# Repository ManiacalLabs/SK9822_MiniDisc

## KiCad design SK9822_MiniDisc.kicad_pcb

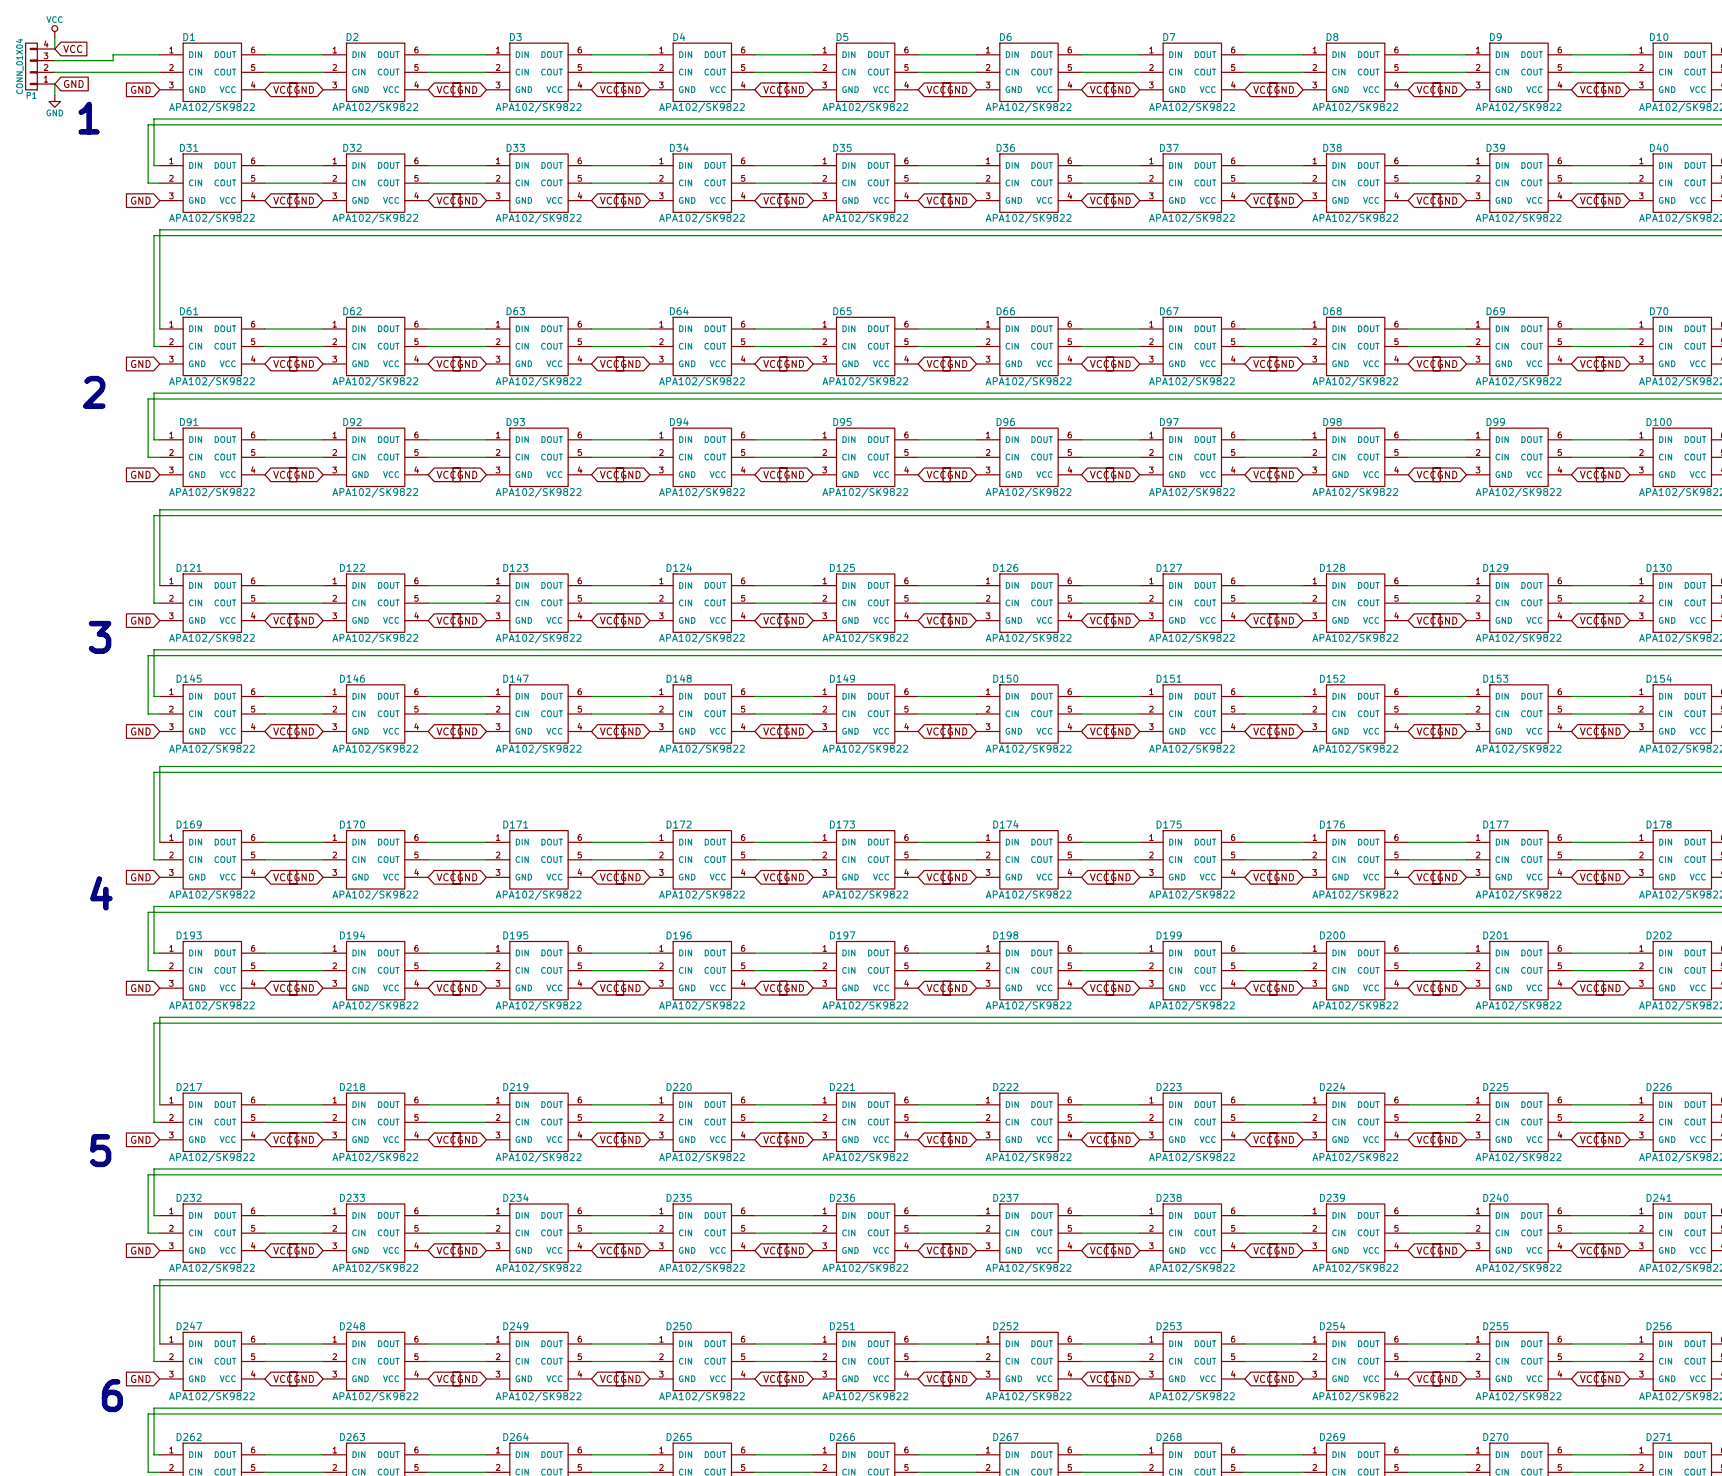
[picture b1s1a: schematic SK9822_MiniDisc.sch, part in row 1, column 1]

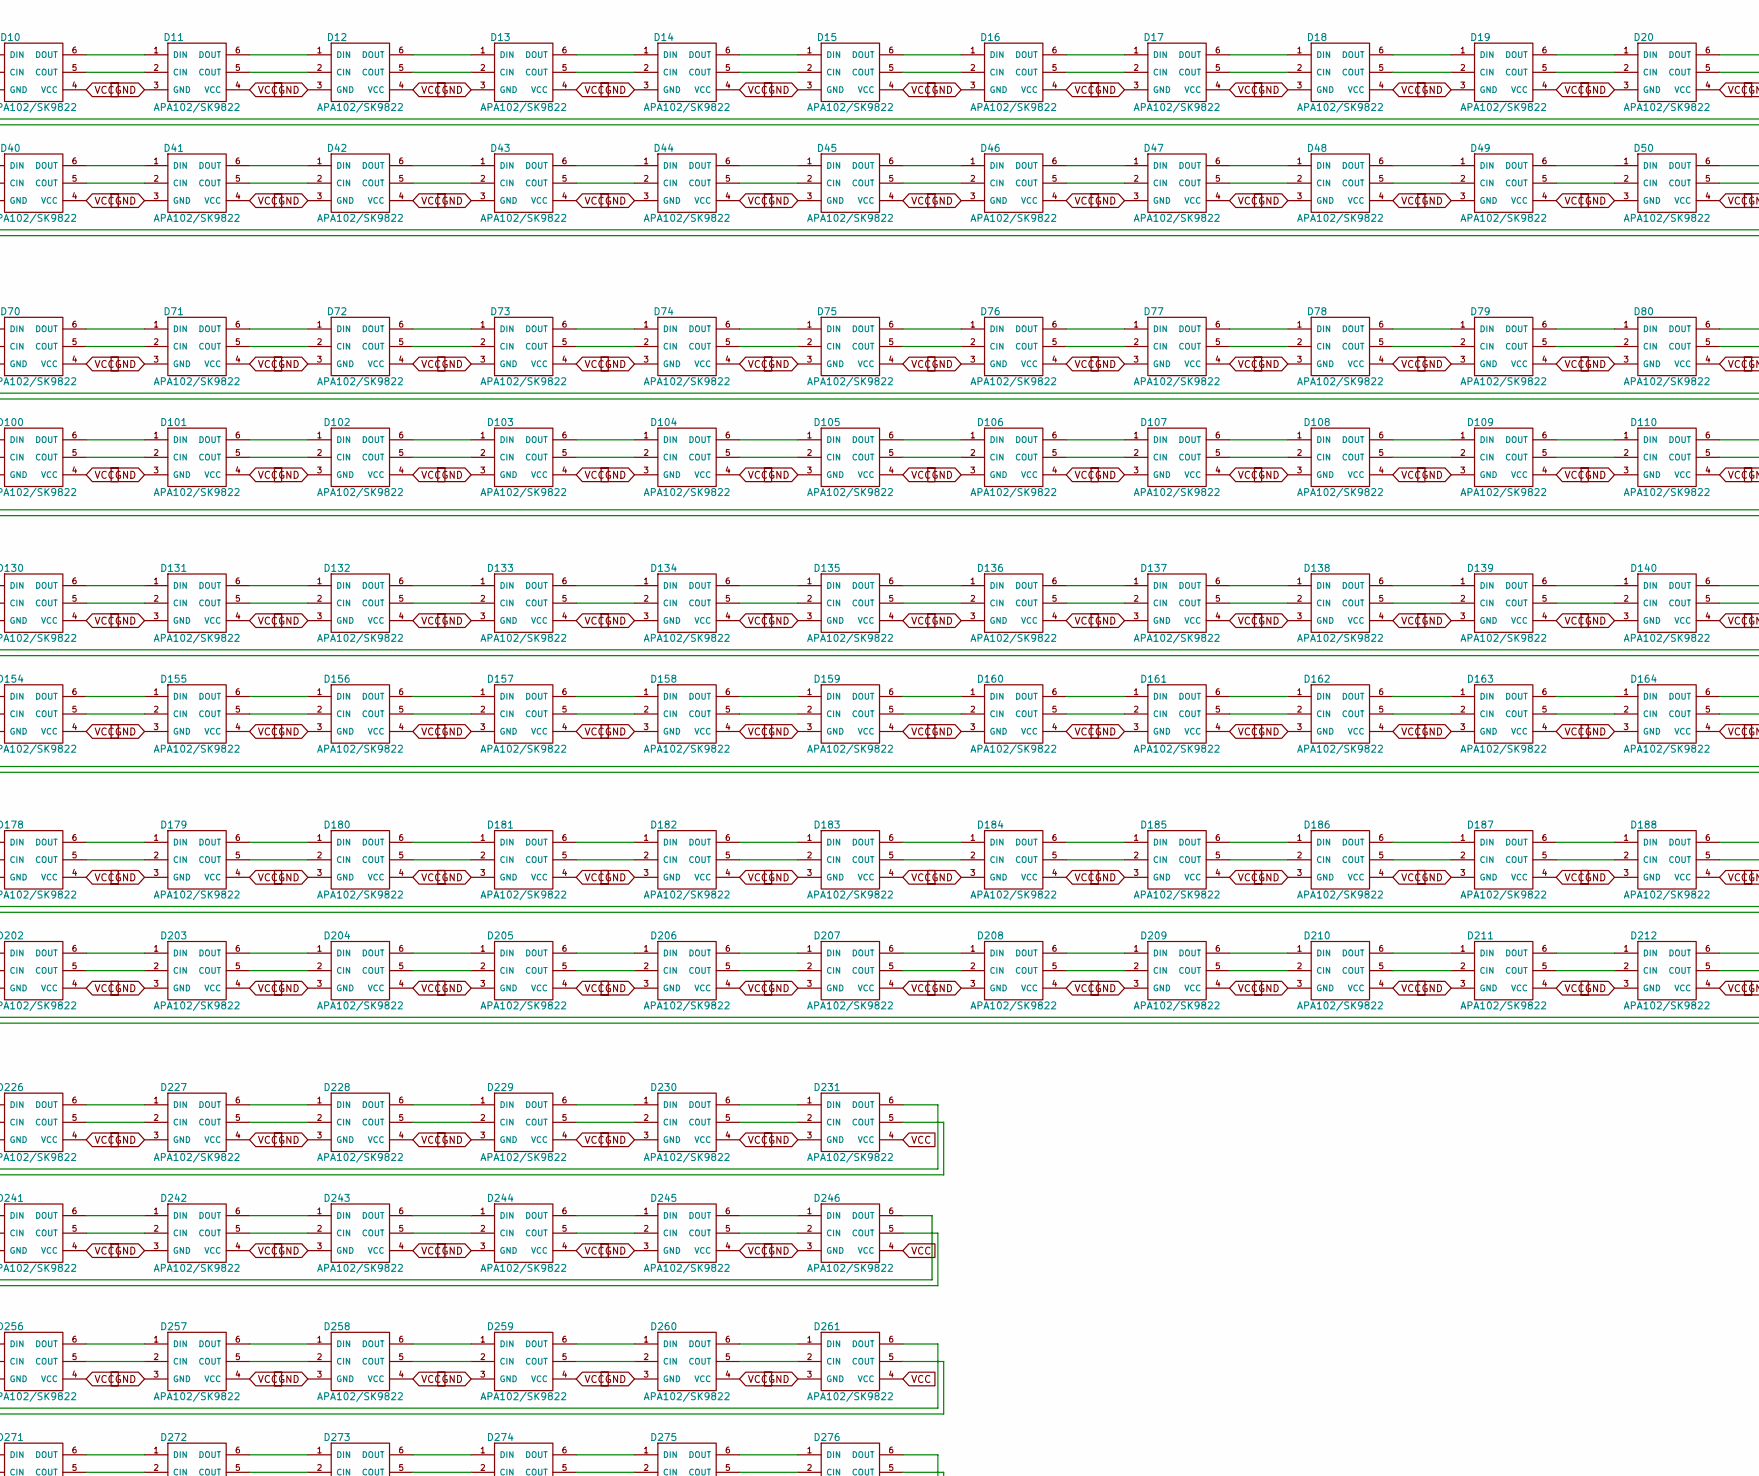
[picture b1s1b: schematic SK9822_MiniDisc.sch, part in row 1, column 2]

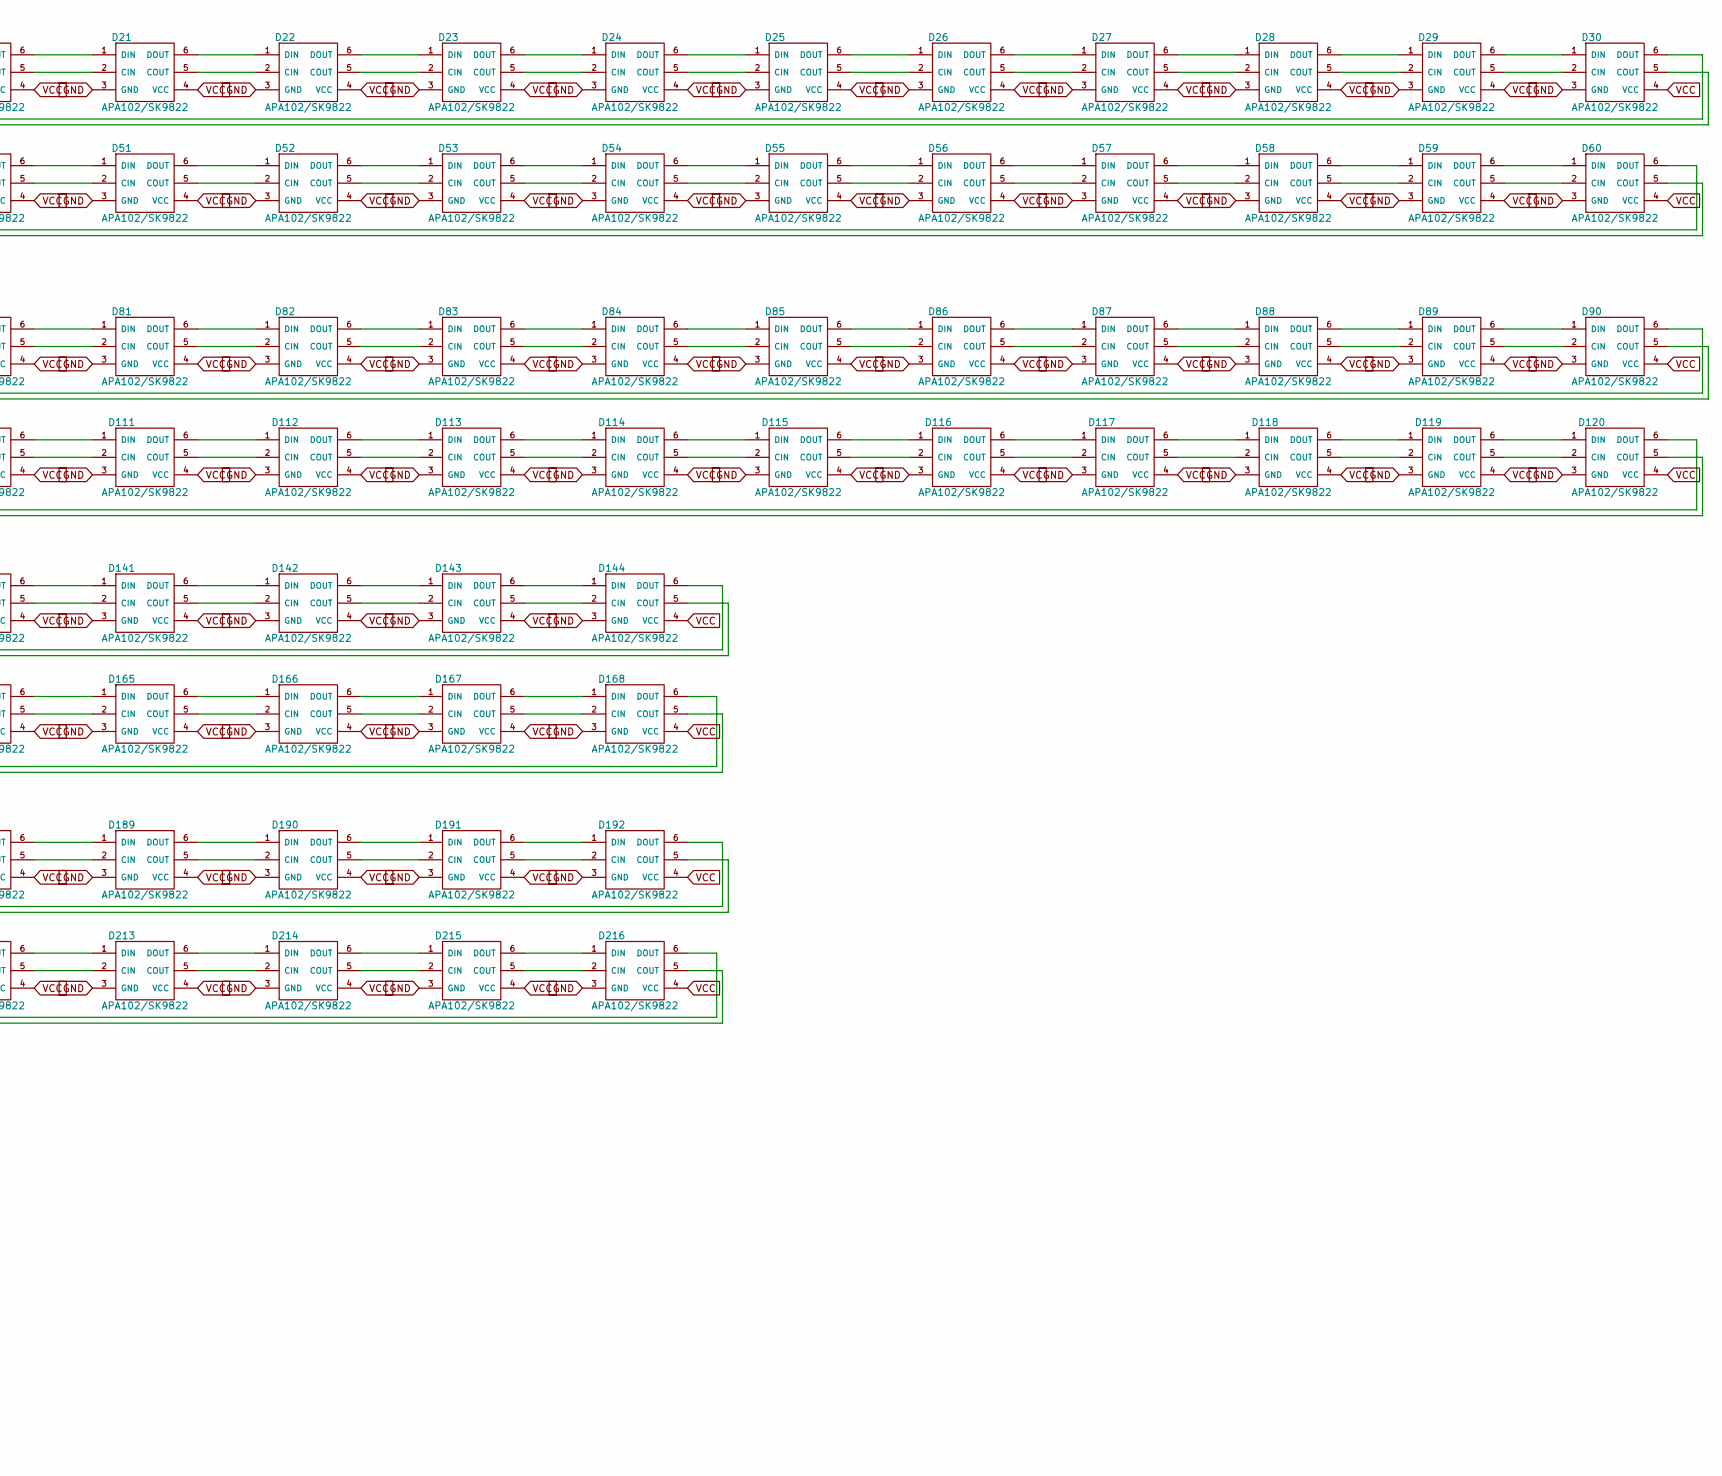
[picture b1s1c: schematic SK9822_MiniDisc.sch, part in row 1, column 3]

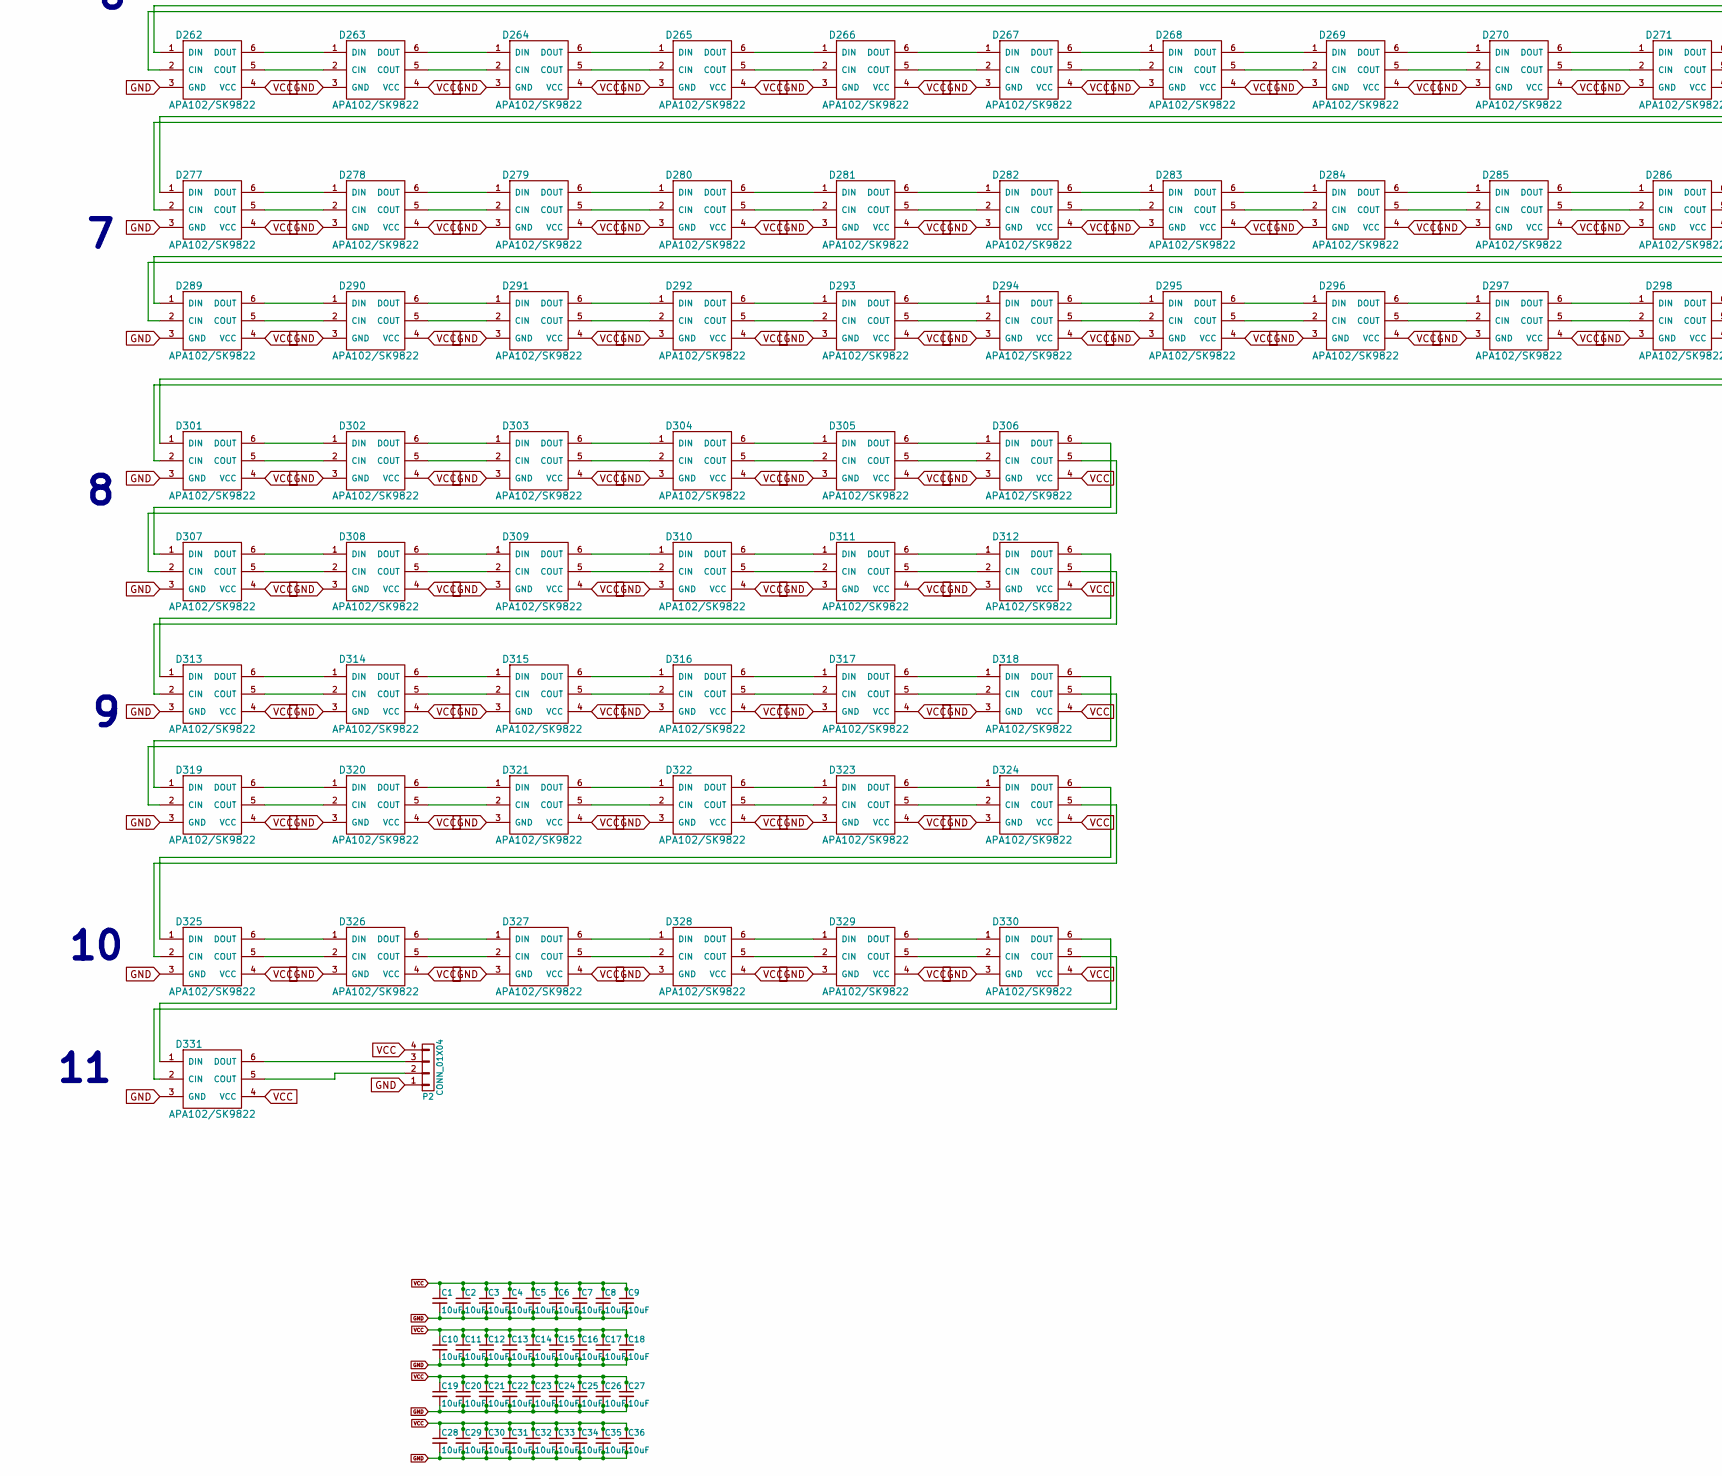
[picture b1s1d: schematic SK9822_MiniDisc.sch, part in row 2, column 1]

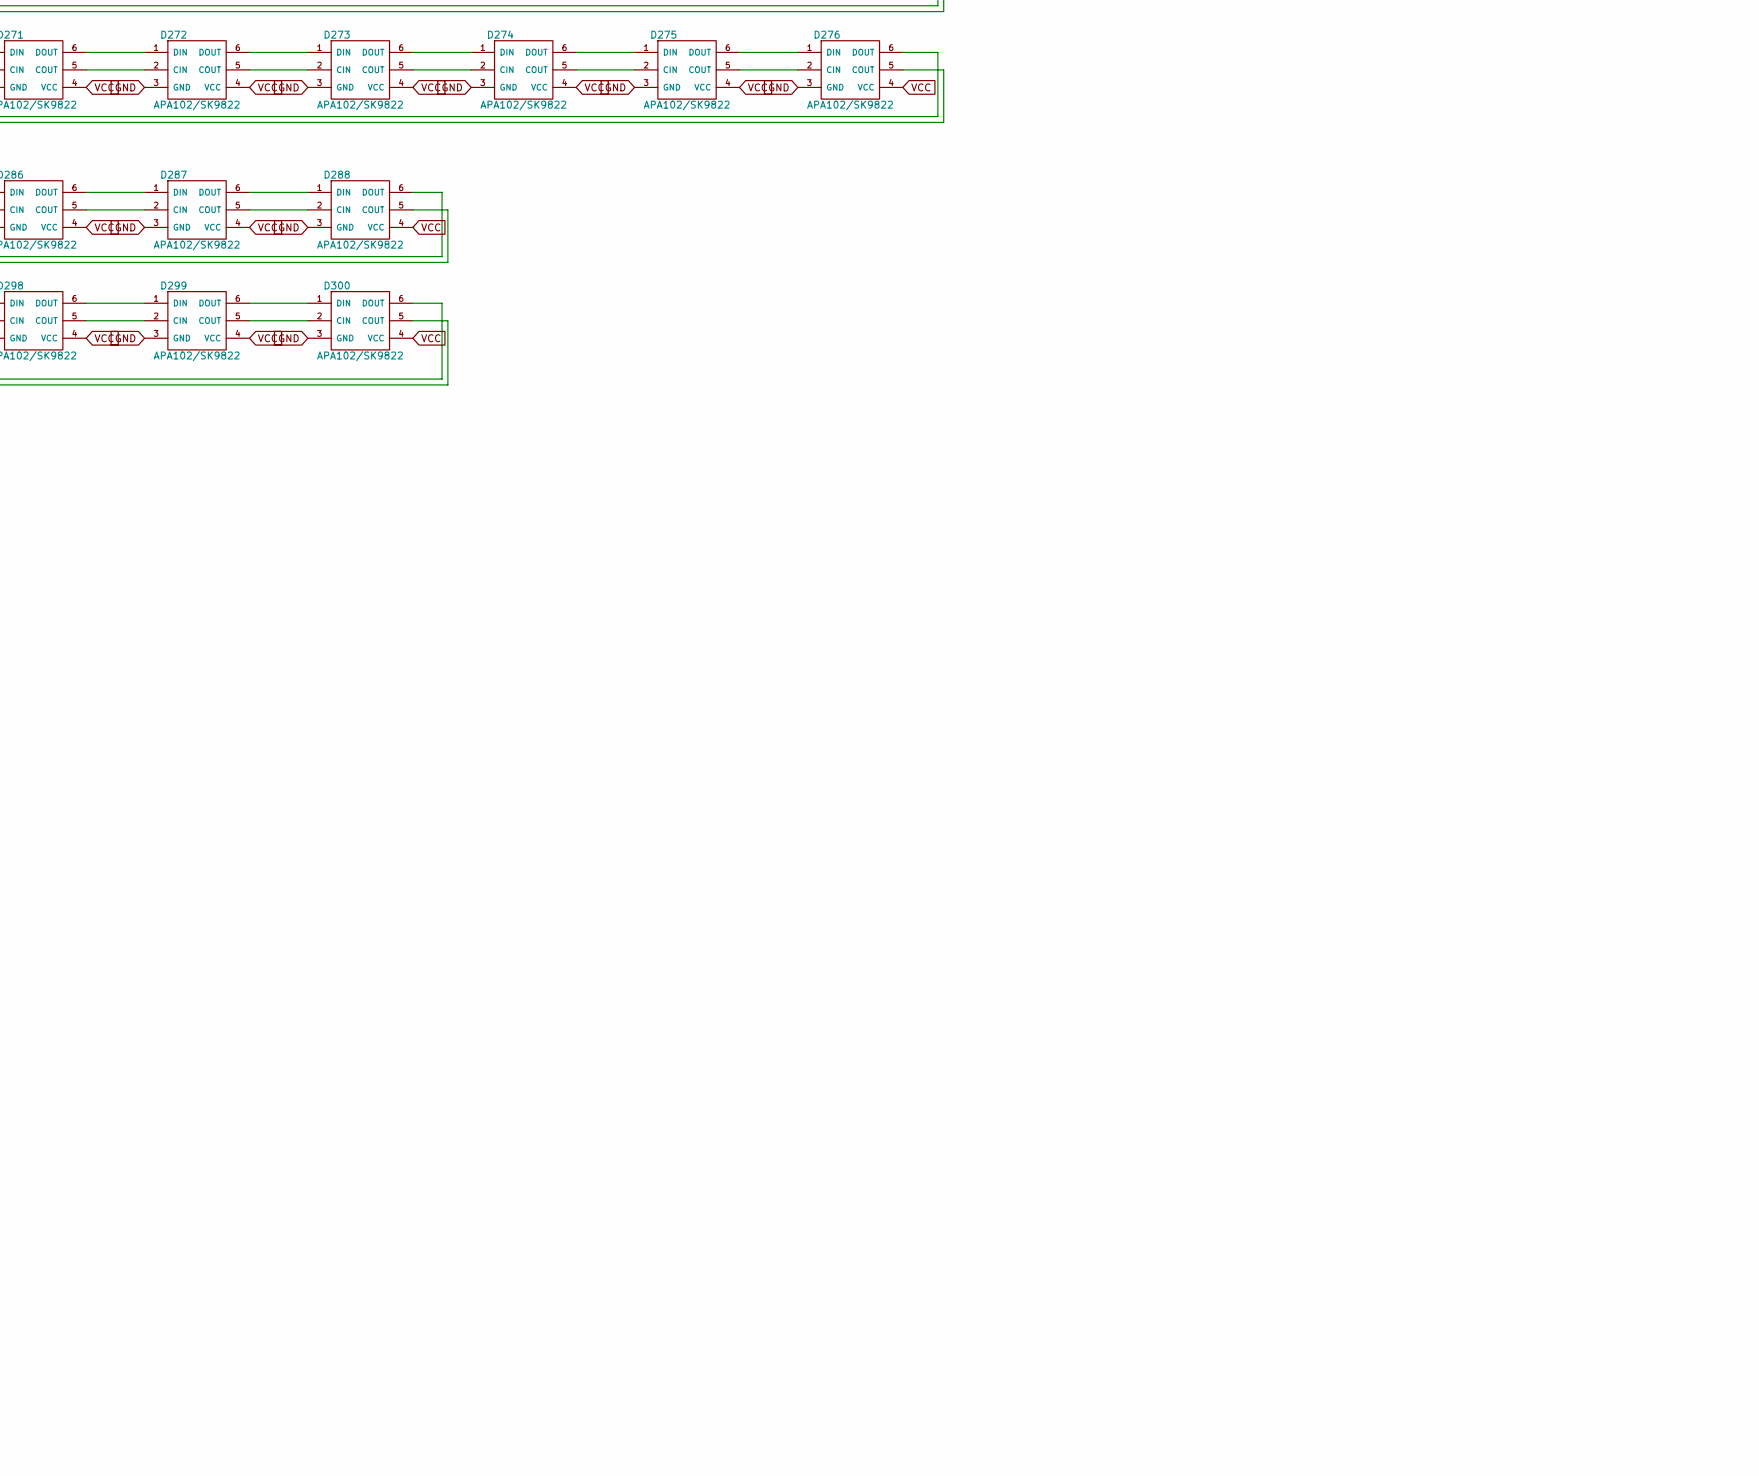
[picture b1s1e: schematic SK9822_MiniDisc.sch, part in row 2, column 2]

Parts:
C1, C2, C3, C4, C5, C6, C7, C8, C9, C10, C11, C12, C13, C14, C15, C16, C17, C18, C19, C20, C21, C22, C23, C24, C25, C26, C27, C28, C29, C30, C31, C32, C33, C34, C35, C36: 10uF; C_0805
D1, D2, D3, D4, D5, D6, D7, D8, D9, D10, D11, D12, D13, D14, D15, D16, D17, D18, D19, D20, D21, D22, D23, D24, D25, D26, D27, D28, D29, D30, D31, D32, D33, D34, D35, D36, D37, D38, D39, D40, D41, D42, D43, D44, D45, D46, D47, D48, D49, D50, D51, D52, D53, D54, D55, D56, D57, D58, D59, D60, D61, D62, D63, D64, D65, D66, D67, D68, D69, D70, D71, D72, D73, D74, D75, D76, D77, D78, D79, D80, D81, D82, D83, D84, D85, D86, D87, D88, D89, D90, D91, D92, D93, D94, D95, D96, D97, D98, D99, D100, D101, D102, D103, D104, D105, D106, D107, D108, D109, D110, D111, D112, D113, D114, D115, D116, D117, D118, D119, D120, D121, D122, D123, D124, D125, D126, D127, D128, D129, D130, D131, D132, D133, D134, D135, D136, D137, D138, D139, D140, D141, D142, D143, D144, D145, D146, D147, D148, D149, D150, D151, D152, D153, D154, D155, D156, D157, D158, D159, D160, D161, D162, D163, D164, D165, D166, D167, D168, D169, D170, D171, D172, D173, D174, D175, D176, D177, D178, D179, D180, D181, D182, D183, D184, D185, D186, D187, D188, D189, D190, D191, D192, D193, D194, D195, D196, D197, D198, D199, D200, D201, D202, D203, D204, D205, D206, D207, D208, D209, D210, D211, D212, D213, D214, D215, D216, D217, D218, D219, D220, D221, D222, D223, D224, D225, D226, D227, D228, D229, D230, D231, D232, D233, D234, D235, D236, D237, D238, D239, D240, D241, D242, D243, D244, D245, D246, D247, D248, D249, D250, D251, D252, D253, D254, D255, D256, D257, D258, D259, D260, D261, D262, D263, D264, D265, D266, D267, D268, D269, D270, D271, D272, D273, D274, D275, D276, D277, D278, D279, D280, D281, D282, D283, D284, D285, D286, D287, D288, D289, D290, D291, D292, D293, D294, D295, D296, D297, D298, D299, D300, D301, D302, D303, D304, D305, D306, D307, D308, D309, D310, D311, D312, D313, D314, D315, D316, D317, D318, D319, D320, D321, D322, D323, D324, D325, D326, D327, D328, D329, D330, D331: APA102/SK9822; SK9822
P1, P2: CONN_01X04; Pin_Header_Angled_1x04

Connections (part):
GND: C1.2, C2.2, C3.2, C4.2, C5.2, C6.2, C7.2, C8.2, C9.2, C10.2, C11.2, C12.2, C13.2, C14.2, C15.2, C16.2, C17.2, C18.2, C19.2, C20.2, C21.2, C22.2, C23.2, C24.2, C25.2, C26.2, C27.2, C28.2, C29.2, C30.2, C31.2, C32.2, C33.2, C34.2, C35.2, C36.2, D1.3 (GND), D2.3 (GND), D3.3 (GND), D4.3 (GND), D5.3 (GND), D6.3 (GND), D7.3 (GND), D8.3 (GND), D9.3 (GND), D10.3 (GND), D11.3 (GND), D12.3 (GND), D13.3 (GND), D14.3 (GND), D15.3 (GND), D16.3 (GND), D17.3 (GND), D18.3 (GND), D19.3 (GND), D20.3 (GND), D21.3 (GND), D22.3 (GND), D23.3 (GND), D24.3 (GND), D25.3 (GND), D26.3 (GND), D27.3 (GND), D28.3 (GND), D29.3 (GND), D30.3 (GND), D31.3 (GND), D32.3 (GND), D33.3 (GND), D34.3 (GND), D35.3 (GND), D36.3 (GND), D37.3 (GND), D38.3 (GND), D39.3 (GND), D40.3 (GND), D41.3 (GND), D42.3 (GND), D43.3 (GND), D44.3 (GND), D45.3 (GND), D46.3 (GND)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
unnamed: D1.1 (DIN), P1.3
unnamed: D1.2 (CIN), P1.2
unnamed: D1.5 (COUT), D2.2 (CIN)
unnamed: D1.6 (DOUT), D2.1 (DIN)
unnamed: D2.5 (COUT), D3.2 (CIN)
unnamed: D2.6 (DOUT), D3.1 (DIN)
unnamed: D3.5 (COUT), D4.2 (CIN)
unnamed: D3.6 (DOUT), D4.1 (DIN)
unnamed: D4.5 (COUT), D5.2 (CIN)
unnamed: D4.6 (DOUT), D5.1 (DIN)
unnamed: D5.5 (COUT), D6.2 (CIN)
unnamed: D5.6 (DOUT), D6.1 (DIN)
unnamed: D6.5 (COUT), D7.2 (CIN)
unnamed: D6.6 (DOUT), D7.1 (DIN)
unnamed: D7.5 (COUT), D8.2 (CIN)
unnamed: D7.6 (DOUT), D8.1 (DIN)
unnamed: D8.5 (COUT), D9.2 (CIN)
unnamed: D8.6 (DOUT), D9.1 (DIN)
unnamed: D9.6 (DOUT), D10.1 (DIN)
unnamed: D9.5 (COUT), D10.2 (CIN)
unnamed: D10.5 (COUT), D11.2 (CIN)
unnamed: D10.6 (DOUT), D11.1 (DIN)
unnamed: D11.5 (COUT), D12.2 (CIN)
unnamed: D11.6 (DOUT), D12.1 (DIN)
unnamed: D12.5 (COUT), D13.2 (CIN)
unnamed: D12.6 (DOUT), D13.1 (DIN)
unnamed: D13.5 (COUT), D14.2 (CIN)
unnamed: D13.6 (DOUT), D14.1 (DIN)
unnamed: D14.5 (COUT), D15.2 (CIN)
unnamed: D14.6 (DOUT), D15.1 (DIN)
unnamed: D15.5 (COUT), D16.2 (CIN)
unnamed: D15.6 (DOUT), D16.1 (DIN)
unnamed: D16.5 (COUT), D17.2 (CIN)
unnamed: D16.6 (DOUT), D17.1 (DIN)
unnamed: D17.5 (COUT), D18.2 (CIN)
unnamed: D17.6 (DOUT), D18.1 (DIN)
unnamed: D18.5 (COUT), D19.2 (CIN)
unnamed: D18.6 (DOUT), D19.1 (DIN)
unnamed: D19.5 (COUT), D20.2 (CIN)
unnamed: D19.6 (DOUT), D20.1 (DIN)
unnamed: D20.5 (COUT), D21.2 (CIN)
unnamed: D20.6 (DOUT), D21.1 (DIN)
unnamed: D21.5 (COUT), D22.2 (CIN)
unnamed: D21.6 (DOUT), D22.1 (DIN)
unnamed: D22.5 (COUT), D23.2 (CIN)
unnamed: D22.6 (DOUT), D23.1 (DIN)
unnamed: D23.5 (COUT), D24.2 (CIN)
unnamed: D23.6 (DOUT), D24.1 (DIN)
unnamed: D24.5 (COUT), D25.2 (CIN)
unnamed: D24.6 (DOUT), D25.1 (DIN)
unnamed: D25.5 (COUT), D26.2 (CIN)
unnamed: D25.6 (DOUT), D26.1 (DIN)
unnamed: D26.5 (COUT), D27.2 (CIN)
unnamed: D26.6 (DOUT), D27.1 (DIN)
unnamed: D27.5 (COUT), D28.2 (CIN)
unnamed: D27.6 (DOUT), D28.1 (DIN)
unnamed: D28.5 (COUT), D29.2 (CIN)
unnamed: D28.6 (DOUT), D29.1 (DIN)
unnamed: D29.5 (COUT), D30.2 (CIN)
unnamed: D29.6 (DOUT), D30.1 (DIN)
unnamed: D30.5 (COUT), D31.2 (CIN)
unnamed: D30.6 (DOUT), D31.1 (DIN)
unnamed: D31.5 (COUT), D32.2 (CIN)
unnamed: D31.6 (DOUT), D32.1 (DIN)
unnamed: D32.5 (COUT), D33.2 (CIN)
unnamed: D32.6 (DOUT), D33.1 (DIN)
unnamed: D33.5 (COUT), D34.2 (CIN)
unnamed: D33.6 (DOUT), D34.1 (DIN)
unnamed: D34.5 (COUT), D35.2 (CIN)
unnamed: D34.6 (DOUT), D35.1 (DIN)
unnamed: D35.5 (COUT), D36.2 (CIN)
unnamed: D35.6 (DOUT), D36.1 (DIN)
unnamed: D36.5 (COUT), D37.2 (CIN)
unnamed: D36.6 (DOUT), D37.1 (DIN)
unnamed: D37.5 (COUT), D38.2 (CIN)
unnamed: D37.6 (DOUT), D38.1 (DIN)
unnamed: D38.5 (COUT), D39.2 (CIN)
unnamed: D38.6 (DOUT), D39.1 (DIN)
unnamed: D39.5 (COUT), D40.2 (CIN)
unnamed: D39.6 (DOUT), D40.1 (DIN)
unnamed: D40.5 (COUT), D41.2 (CIN)
unnamed: D40.6 (DOUT), D41.1 (DIN)
unnamed: D41.5 (COUT), D42.2 (CIN)
unnamed: D41.6 (DOUT), D42.1 (DIN)
unnamed: D42.5 (COUT), D43.2 (CIN)
unnamed: D42.6 (DOUT), D43.1 (DIN)
unnamed: D43.5 (COUT), D44.2 (CIN)
unnamed: D43.6 (DOUT), D44.1 (DIN)
unnamed: D44.5 (COUT), D45.2 (CIN)
unnamed: D44.6 (DOUT), D45.1 (DIN)
unnamed: D45.5 (COUT), D46.2 (CIN)
unnamed: D45.6 (DOUT), D46.1 (DIN)
unnamed: D46.5 (COUT), D47.2 (CIN)
unnamed: D46.6 (DOUT), D47.1 (DIN)
unnamed: D47.5 (COUT), D48.2 (CIN)
unnamed: D47.6 (DOUT), D48.1 (DIN)
unnamed: D48.5 (COUT), D49.2 (CIN)
unnamed: D48.6 (DOUT), D49.1 (DIN)
unnamed: D49.5 (COUT), D50.2 (CIN)
unnamed: D49.6 (DOUT), D50.1 (DIN)
unnamed: D50.5 (COUT), D51.2 (CIN)
unnamed: D50.6 (DOUT), D51.1 (DIN)
unnamed: D51.5 (COUT), D52.2 (CIN)
unnamed: D51.6 (DOUT), D52.1 (DIN)
unnamed: D52.5 (COUT), D53.2 (CIN)
unnamed: D52.6 (DOUT), D53.1 (DIN)
unnamed: D53.5 (COUT), D54.2 (CIN)
unnamed: D53.6 (DOUT), D54.1 (DIN)
unnamed: D54.5 (COUT), D55.2 (CIN)
unnamed: D54.6 (DOUT), D55.1 (DIN)
unnamed: D55.5 (COUT), D56.2 (CIN)
unnamed: D55.6 (DOUT), D56.1 (DIN)
unnamed: D56.5 (COUT), D57.2 (CIN)
unnamed: D56.6 (DOUT), D57.1 (DIN)
unnamed: D57.5 (COUT), D58.2 (CIN)
unnamed: D57.6 (DOUT), D58.1 (DIN)
unnamed: D58.5 (COUT), D59.2 (CIN)
unnamed: D58.6 (DOUT), D59.1 (DIN)
unnamed: D59.5 (COUT), D60.2 (CIN)
unnamed: D59.6 (DOUT), D60.1 (DIN)
unnamed: D60.5 (COUT), D61.2 (CIN)
unnamed: D60.6 (DOUT), D61.1 (DIN)
unnamed: D61.5 (COUT), D62.2 (CIN)
unnamed: D61.6 (DOUT), D62.1 (DIN)
unnamed: D62.5 (COUT), D63.2 (CIN)
unnamed: D62.6 (DOUT), D63.1 (DIN)
unnamed: D63.5 (COUT), D64.2 (CIN)
unnamed: D63.6 (DOUT), D64.1 (DIN)
unnamed: D64.5 (COUT), D65.2 (CIN)
unnamed: D64.6 (DOUT), D65.1 (DIN)
unnamed: D65.5 (COUT), D66.2 (CIN)
unnamed: D65.6 (DOUT), D66.1 (DIN)
unnamed: D66.5 (COUT), D67.2 (CIN)
unnamed: D66.6 (DOUT), D67.1 (DIN)
unnamed: D67.5 (COUT), D68.2 (CIN)
unnamed: D67.6 (DOUT), D68.1 (DIN)
unnamed: D68.5 (COUT), D69.2 (CIN)
unnamed: D68.6 (DOUT), D69.1 (DIN)
unnamed: D69.5 (COUT), D70.2 (CIN)
unnamed: D69.6 (DOUT), D70.1 (DIN)
unnamed: D70.5 (COUT), D71.2 (CIN)
unnamed: D70.6 (DOUT), D71.1 (DIN)
unnamed: D71.5 (COUT), D72.2 (CIN)
unnamed: D71.6 (DOUT), D72.1 (DIN)
unnamed: D72.5 (COUT), D73.2 (CIN)
unnamed: D72.6 (DOUT), D73.1 (DIN)
unnamed: D73.5 (COUT), D74.2 (CIN)
unnamed: D73.6 (DOUT), D74.1 (DIN)
unnamed: D74.5 (COUT), D75.2 (CIN)
unnamed: D74.6 (DOUT), D75.1 (DIN)
unnamed: D75.5 (COUT), D76.2 (CIN)
unnamed: D75.6 (DOUT), D76.1 (DIN)
unnamed: D76.5 (COUT), D77.2 (CIN)
unnamed: D76.6 (DOUT), D77.1 (DIN)
unnamed: D77.5 (COUT), D78.2 (CIN)
unnamed: D77.6 (DOUT), D78.1 (DIN)
unnamed: D78.5 (COUT), D79.2 (CIN)
unnamed: D78.6 (DOUT), D79.1 (DIN)
unnamed: D79.5 (COUT), D80.2 (CIN)
unnamed: D79.6 (DOUT), D80.1 (DIN)
unnamed: D80.5 (COUT), D81.2 (CIN)
unnamed: D80.6 (DOUT), D81.1 (DIN)
unnamed: D81.5 (COUT), D82.2 (CIN)
unnamed: D81.6 (DOUT), D82.1 (DIN)
unnamed: D82.5 (COUT), D83.2 (CIN)
unnamed: D82.6 (DOUT), D83.1 (DIN)
unnamed: D83.5 (COUT), D84.2 (CIN)
unnamed: D83.6 (DOUT), D84.1 (DIN)
unnamed: D84.5 (COUT), D85.2 (CIN)
unnamed: D84.6 (DOUT), D85.1 (DIN)
unnamed: D85.5 (COUT), D86.2 (CIN)
unnamed: D85.6 (DOUT), D86.1 (DIN)
unnamed: D86.5 (COUT), D87.2 (CIN)
unnamed: D86.6 (DOUT), D87.1 (DIN)
unnamed: D87.5 (COUT), D88.2 (CIN)
unnamed: D87.6 (DOUT), D88.1 (DIN)
unnamed: D88.5 (COUT), D89.2 (CIN)
unnamed: D88.6 (DOUT), D89.1 (DIN)
unnamed: D89.5 (COUT), D90.2 (CIN)
unnamed: D89.6 (DOUT), D90.1 (DIN)
unnamed: D90.5 (COUT), D91.2 (CIN)
unnamed: D90.6 (DOUT), D91.1 (DIN)
unnamed: D91.5 (COUT), D92.2 (CIN)
unnamed: D91.6 (DOUT), D92.1 (DIN)
unnamed: D92.5 (COUT), D93.2 (CIN)
unnamed: D92.6 (DOUT), D93.1 (DIN)
unnamed: D93.5 (COUT), D94.2 (CIN)
unnamed: D93.6 (DOUT), D94.1 (DIN)
unnamed: D94.5 (COUT), D95.2 (CIN)
unnamed: D94.6 (DOUT), D95.1 (DIN)
unnamed: D95.5 (COUT), D96.2 (CIN)
unnamed: D95.6 (DOUT), D96.1 (DIN)
unnamed: D96.5 (COUT), D97.2 (CIN)
unnamed: D96.6 (DOUT), D97.1 (DIN)
unnamed: D97.5 (COUT), D98.2 (CIN)
unnamed: D97.6 (DOUT), D98.1 (DIN)
unnamed: D98.5 (COUT), D99.2 (CIN)
unnamed: D98.6 (DOUT), D99.1 (DIN)
unnamed: D99.6 (DOUT), D100.1 (DIN)
unnamed: D99.5 (COUT), D100.2 (CIN)
unnamed: D100.5 (COUT), D101.2 (CIN)
unnamed: D100.6 (DOUT), D101.1 (DIN)
unnamed: D101.5 (COUT), D102.2 (CIN)
unnamed: D101.6 (DOUT), D102.1 (DIN)
unnamed: D102.5 (COUT), D103.2 (CIN)
unnamed: D102.6 (DOUT), D103.1 (DIN)
unnamed: D103.5 (COUT), D104.2 (CIN)
unnamed: D103.6 (DOUT), D104.1 (DIN)
unnamed: D104.5 (COUT), D105.2 (CIN)
unnamed: D104.6 (DOUT), D105.1 (DIN)
unnamed: D105.5 (COUT), D106.2 (CIN)
unnamed: D105.6 (DOUT), D106.1 (DIN)
unnamed: D106.5 (COUT), D107.2 (CIN)
unnamed: D106.6 (DOUT), D107.1 (DIN)
unnamed: D107.5 (COUT), D108.2 (CIN)
unnamed: D107.6 (DOUT), D108.1 (DIN)
unnamed: D108.5 (COUT), D109.2 (CIN)
unnamed: D108.6 (DOUT), D109.1 (DIN)
unnamed: D109.5 (COUT), D110.2 (CIN)
unnamed: D109.6 (DOUT), D110.1 (DIN)
unnamed: D110.5 (COUT), D111.2 (CIN)
unnamed: D110.6 (DOUT), D111.1 (DIN)
unnamed: D111.5 (COUT), D112.2 (CIN)
unnamed: D111.6 (DOUT), D112.1 (DIN)
unnamed: D112.5 (COUT), D113.2 (CIN)
unnamed: D112.6 (DOUT), D113.1 (DIN)
unnamed: D113.5 (COUT), D114.2 (CIN)
unnamed: D113.6 (DOUT), D114.1 (DIN)
unnamed: D114.5 (COUT), D115.2 (CIN)
unnamed: D114.6 (DOUT), D115.1 (DIN)
unnamed: D115.5 (COUT), D116.2 (CIN)
unnamed: D115.6 (DOUT), D116.1 (DIN)
unnamed: D116.5 (COUT), D117.2 (CIN)
unnamed: D116.6 (DOUT), D117.1 (DIN)
unnamed: D117.5 (COUT), D118.2 (CIN)
unnamed: D117.6 (DOUT), D118.1 (DIN)
unnamed: D118.5 (COUT), D119.2 (CIN)
unnamed: D118.6 (DOUT), D119.1 (DIN)
unnamed: D119.5 (COUT), D120.2 (CIN)
unnamed: D119.6 (DOUT), D120.1 (DIN)
unnamed: D120.5 (COUT), D121.2 (CIN)
unnamed: D120.6 (DOUT), D121.1 (DIN)
unnamed: D121.5 (COUT), D122.2 (CIN)
unnamed: D121.6 (DOUT), D122.1 (DIN)
unnamed: D122.5 (COUT), D123.2 (CIN)
unnamed: D122.6 (DOUT), D123.1 (DIN)
unnamed: D123.5 (COUT), D124.2 (CIN)
unnamed: D123.6 (DOUT), D124.1 (DIN)
unnamed: D124.5 (COUT), D125.2 (CIN)
unnamed: D124.6 (DOUT), D125.1 (DIN)
unnamed: D125.5 (COUT), D126.2 (CIN)
unnamed: D125.6 (DOUT), D126.1 (DIN)
unnamed: D126.5 (COUT), D127.2 (CIN)
unnamed: D126.6 (DOUT), D127.1 (DIN)
unnamed: D127.5 (COUT), D128.2 (CIN)
unnamed: D127.6 (DOUT), D128.1 (DIN)
unnamed: D128.5 (COUT), D129.2 (CIN)
unnamed: D128.6 (DOUT), D129.1 (DIN)
unnamed: D129.5 (COUT), D130.2 (CIN)
unnamed: D129.6 (DOUT), D130.1 (DIN)
unnamed: D130.5 (COUT), D131.2 (CIN)
unnamed: D130.6 (DOUT), D131.1 (DIN)
unnamed: D131.5 (COUT), D132.2 (CIN)
unnamed: D131.6 (DOUT), D132.1 (DIN)
unnamed: D132.5 (COUT), D133.2 (CIN)
unnamed: D132.6 (DOUT), D133.1 (DIN)
unnamed: D133.5 (COUT), D134.2 (CIN)
unnamed: D133.6 (DOUT), D134.1 (DIN)
unnamed: D134.5 (COUT), D135.2 (CIN)
unnamed: D134.6 (DOUT), D135.1 (DIN)
unnamed: D135.5 (COUT), D136.2 (CIN)
unnamed: D135.6 (DOUT), D136.1 (DIN)
unnamed: D136.5 (COUT), D137.2 (CIN)
unnamed: D136.6 (DOUT), D137.1 (DIN)
unnamed: D137.5 (COUT), D138.2 (CIN)
unnamed: D137.6 (DOUT), D138.1 (DIN)
unnamed: D138.5 (COUT), D139.2 (CIN)
unnamed: D138.6 (DOUT), D139.1 (DIN)
unnamed: D139.5 (COUT), D140.2 (CIN)
unnamed: D139.6 (DOUT), D140.1 (DIN)
unnamed: D140.5 (COUT), D141.2 (CIN)
unnamed: D140.6 (DOUT), D141.1 (DIN)
unnamed: D141.5 (COUT), D142.2 (CIN)
unnamed: D141.6 (DOUT), D142.1 (DIN)
unnamed: D142.5 (COUT), D143.2 (CIN)
unnamed: D142.6 (DOUT), D143.1 (DIN)
unnamed: D143.5 (COUT), D144.2 (CIN)
unnamed: D143.6 (DOUT), D144.1 (DIN)
unnamed: D144.5 (COUT), D145.2 (CIN)
unnamed: D144.6 (DOUT), D145.1 (DIN)
unnamed: D145.5 (COUT), D146.2 (CIN)
unnamed: D145.6 (DOUT), D146.1 (DIN)
unnamed: D146.5 (COUT), D147.2 (CIN)
unnamed: D146.6 (DOUT), D147.1 (DIN)
unnamed: D147.5 (COUT), D148.2 (CIN)
unnamed: D147.6 (DOUT), D148.1 (DIN)
unnamed: D148.5 (COUT), D149.2 (CIN)
unnamed: D148.6 (DOUT), D149.1 (DIN)
unnamed: D149.5 (COUT), D150.2 (CIN)
unnamed: D149.6 (DOUT), D150.1 (DIN)
unnamed: D150.5 (COUT), D151.2 (CIN)
unnamed: D150.6 (DOUT), D151.1 (DIN)
unnamed: D151.5 (COUT), D152.2 (CIN)
unnamed: D151.6 (DOUT), D152.1 (DIN)
unnamed: D152.5 (COUT), D153.2 (CIN)
unnamed: D152.6 (DOUT), D153.1 (DIN)
unnamed: D153.5 (COUT), D154.2 (CIN)
unnamed: D153.6 (DOUT), D154.1 (DIN)
unnamed: D154.5 (COUT), D155.2 (CIN)
unnamed: D154.6 (DOUT), D155.1 (DIN)
unnamed: D155.5 (COUT), D156.2 (CIN)
unnamed: D155.6 (DOUT), D156.1 (DIN)
unnamed: D156.5 (COUT), D157.2 (CIN)
unnamed: D156.6 (DOUT), D157.1 (DIN)
unnamed: D157.5 (COUT), D158.2 (CIN)
unnamed: D157.6 (DOUT), D158.1 (DIN)
unnamed: D158.5 (COUT), D159.2 (CIN)
unnamed: D158.6 (DOUT), D159.1 (DIN)
unnamed: D159.5 (COUT), D160.2 (CIN)
unnamed: D159.6 (DOUT), D160.1 (DIN)
unnamed: D160.5 (COUT), D161.2 (CIN)
unnamed: D160.6 (DOUT), D161.1 (DIN)
unnamed: D161.5 (COUT), D162.2 (CIN)
unnamed: D161.6 (DOUT), D162.1 (DIN)
unnamed: D162.5 (COUT), D163.2 (CIN)
unnamed: D162.6 (DOUT), D163.1 (DIN)
unnamed: D163.5 (COUT), D164.2 (CIN)
unnamed: D163.6 (DOUT), D164.1 (DIN)
unnamed: D164.5 (COUT), D165.2 (CIN)
unnamed: D164.6 (DOUT), D165.1 (DIN)
unnamed: D165.5 (COUT), D166.2 (CIN)
unnamed: D165.6 (DOUT), D166.1 (DIN)
unnamed: D166.5 (COUT), D167.2 (CIN)
unnamed: D166.6 (DOUT), D167.1 (DIN)
unnamed: D167.5 (COUT), D168.2 (CIN)
unnamed: D167.6 (DOUT), D168.1 (DIN)
unnamed: D168.5 (COUT), D169.2 (CIN)
unnamed: D168.6 (DOUT), D169.1 (DIN)
unnamed: D169.5 (COUT), D170.2 (CIN)
unnamed: D169.6 (DOUT), D170.1 (DIN)
unnamed: D170.5 (COUT), D171.2 (CIN)
unnamed: D170.6 (DOUT), D171.1 (DIN)
unnamed: D171.5 (COUT), D172.2 (CIN)
unnamed: D171.6 (DOUT), D172.1 (DIN)
unnamed: D172.5 (COUT), D173.2 (CIN)
unnamed: D172.6 (DOUT), D173.1 (DIN)
unnamed: D173.5 (COUT), D174.2 (CIN)
unnamed: D173.6 (DOUT), D174.1 (DIN)
unnamed: D174.5 (COUT), D175.2 (CIN)
unnamed: D174.6 (DOUT), D175.1 (DIN)
unnamed: D175.5 (COUT), D176.2 (CIN)
unnamed: D175.6 (DOUT), D176.1 (DIN)
unnamed: D176.5 (COUT), D177.2 (CIN)
unnamed: D176.6 (DOUT), D177.1 (DIN)
unnamed: D177.5 (COUT), D178.2 (CIN)
unnamed: D177.6 (DOUT), D178.1 (DIN)
unnamed: D178.5 (COUT), D179.2 (CIN)
unnamed: D178.6 (DOUT), D179.1 (DIN)
unnamed: D179.5 (COUT), D180.2 (CIN)
unnamed: D179.6 (DOUT), D180.1 (DIN)
unnamed: D180.5 (COUT), D181.2 (CIN)
unnamed: D180.6 (DOUT), D181.1 (DIN)
unnamed: D181.5 (COUT), D182.2 (CIN)
unnamed: D181.6 (DOUT), D182.1 (DIN)
unnamed: D182.5 (COUT), D183.2 (CIN)
unnamed: D182.6 (DOUT), D183.1 (DIN)
unnamed: D183.5 (COUT), D184.2 (CIN)
unnamed: D183.6 (DOUT), D184.1 (DIN)
unnamed: D184.5 (COUT), D185.2 (CIN)
unnamed: D184.6 (DOUT), D185.1 (DIN)
unnamed: D185.5 (COUT), D186.2 (CIN)
unnamed: D185.6 (DOUT), D186.1 (DIN)
unnamed: D186.5 (COUT), D187.2 (CIN)
unnamed: D186.6 (DOUT), D187.1 (DIN)
unnamed: D187.5 (COUT), D188.2 (CIN)
unnamed: D187.6 (DOUT), D188.1 (DIN)
unnamed: D188.5 (COUT), D189.2 (CIN)
unnamed: D188.6 (DOUT), D189.1 (DIN)
unnamed: D189.5 (COUT), D190.2 (CIN)
unnamed: D189.6 (DOUT), D190.1 (DIN)
unnamed: D190.5 (COUT), D191.2 (CIN)
unnamed: D190.6 (DOUT), D191.1 (DIN)
unnamed: D191.5 (COUT), D192.2 (CIN)
unnamed: D191.6 (DOUT), D192.1 (DIN)
unnamed: D192.5 (COUT), D193.2 (CIN)
unnamed: D192.6 (DOUT), D193.1 (DIN)
unnamed: D193.5 (COUT), D194.2 (CIN)
unnamed: D193.6 (DOUT), D194.1 (DIN)
unnamed: D194.5 (COUT), D195.2 (CIN)
unnamed: D194.6 (DOUT), D195.1 (DIN)
unnamed: D195.5 (COUT), D196.2 (CIN)
unnamed: D195.6 (DOUT), D196.1 (DIN)
unnamed: D196.5 (COUT), D197.2 (CIN)
unnamed: D196.6 (DOUT), D197.1 (DIN)
unnamed: D197.5 (COUT), D198.2 (CIN)
unnamed: D197.6 (DOUT), D198.1 (DIN)
unnamed: D198.5 (COUT), D199.2 (CIN)
unnamed: D198.6 (DOUT), D199.1 (DIN)
unnamed: D199.5 (COUT), D200.2 (CIN)
unnamed: D199.6 (DOUT), D200.1 (DIN)
unnamed: D200.5 (COUT), D201.2 (CIN)
unnamed: D200.6 (DOUT), D201.1 (DIN)
unnamed: D201.5 (COUT), D202.2 (CIN)
unnamed: D201.6 (DOUT), D202.1 (DIN)
unnamed: D202.5 (COUT), D203.2 (CIN)
unnamed: D202.6 (DOUT), D203.1 (DIN)
unnamed: D203.5 (COUT), D204.2 (CIN)
unnamed: D203.6 (DOUT), D204.1 (DIN)
unnamed: D204.5 (COUT), D205.2 (CIN)
unnamed: D204.6 (DOUT), D205.1 (DIN)
unnamed: D205.5 (COUT), D206.2 (CIN)
unnamed: D205.6 (DOUT), D206.1 (DIN)
unnamed: D206.5 (COUT), D207.2 (CIN)
unnamed: D206.6 (DOUT), D207.1 (DIN)
unnamed: D207.5 (COUT), D208.2 (CIN)
unnamed: D207.6 (DOUT), D208.1 (DIN)
unnamed: D208.5 (COUT), D209.2 (CIN)
unnamed: D208.6 (DOUT), D209.1 (DIN)
unnamed: D209.5 (COUT), D210.2 (CIN)
unnamed: D209.6 (DOUT), D210.1 (DIN)
unnamed: D210.5 (COUT), D211.2 (CIN)
unnamed: D210.6 (DOUT), D211.1 (DIN)
unnamed: D211.5 (COUT), D212.2 (CIN)
unnamed: D211.6 (DOUT), D212.1 (DIN)
unnamed: D212.5 (COUT), D213.2 (CIN)
unnamed: D212.6 (DOUT), D213.1 (DIN)
unnamed: D213.5 (COUT), D214.2 (CIN)
unnamed: D213.6 (DOUT), D214.1 (DIN)
unnamed: D214.5 (COUT), D215.2 (CIN)
unnamed: D214.6 (DOUT), D215.1 (DIN)
unnamed: D215.5 (COUT), D216.2 (CIN)
unnamed: D215.6 (DOUT), D216.1 (DIN)
unnamed: D216.5 (COUT), D217.2 (CIN)
unnamed: D216.6 (DOUT), D217.1 (DIN)
unnamed: D217.5 (COUT), D218.2 (CIN)
unnamed: D217.6 (DOUT), D218.1 (DIN)
unnamed: D218.5 (COUT), D219.2 (CIN)
unnamed: D218.6 (DOUT), D219.1 (DIN)
unnamed: D219.5 (COUT), D220.2 (CIN)
unnamed: D219.6 (DOUT), D220.1 (DIN)
unnamed: D220.5 (COUT), D221.2 (CIN)
unnamed: D220.6 (DOUT), D221.1 (DIN)
unnamed: D221.5 (COUT), D222.2 (CIN)
unnamed: D221.6 (DOUT), D222.1 (DIN)
unnamed: D222.5 (COUT), D223.2 (CIN)
unnamed: D222.6 (DOUT), D223.1 (DIN)
unnamed: D223.5 (COUT), D224.2 (CIN)
unnamed: D223.6 (DOUT), D224.1 (DIN)
unnamed: D224.5 (COUT), D225.2 (CIN)
unnamed: D224.6 (DOUT), D225.1 (DIN)
unnamed: D225.5 (COUT), D226.2 (CIN)
unnamed: D225.6 (DOUT), D226.1 (DIN)
unnamed: D226.5 (COUT), D227.2 (CIN)
unnamed: D226.6 (DOUT), D227.1 (DIN)
unnamed: D227.5 (COUT), D228.2 (CIN)
unnamed: D227.6 (DOUT), D228.1 (DIN)
unnamed: D228.5 (COUT), D229.2 (CIN)
unnamed: D228.6 (DOUT), D229.1 (DIN)
unnamed: D229.5 (COUT), D230.2 (CIN)
unnamed: D229.6 (DOUT), D230.1 (DIN)
unnamed: D230.5 (COUT), D231.2 (CIN)
unnamed: D230.6 (DOUT), D231.1 (DIN)
unnamed: D231.5 (COUT), D232.2 (CIN)
unnamed: D231.6 (DOUT), D232.1 (DIN)
unnamed: D232.5 (COUT), D233.2 (CIN)
unnamed: D232.6 (DOUT), D233.1 (DIN)
unnamed: D233.5 (COUT), D234.2 (CIN)
unnamed: D233.6 (DOUT), D234.1 (DIN)
unnamed: D234.5 (COUT), D235.2 (CIN)
unnamed: D234.6 (DOUT), D235.1 (DIN)
unnamed: D235.5 (COUT), D236.2 (CIN)
unnamed: D235.6 (DOUT), D236.1 (DIN)
unnamed: D236.5 (COUT), D237.2 (CIN)
unnamed: D236.6 (DOUT), D237.1 (DIN)
unnamed: D237.5 (COUT), D238.2 (CIN)
unnamed: D237.6 (DOUT), D238.1 (DIN)
unnamed: D238.5 (COUT), D239.2 (CIN)
unnamed: D238.6 (DOUT), D239.1 (DIN)
unnamed: D239.5 (COUT), D240.2 (CIN)
unnamed: D239.6 (DOUT), D240.1 (DIN)
unnamed: D240.5 (COUT), D241.2 (CIN)
unnamed: D240.6 (DOUT), D241.1 (DIN)
unnamed: D241.5 (COUT), D242.2 (CIN)
unnamed: D241.6 (DOUT), D242.1 (DIN)
unnamed: D242.5 (COUT), D243.2 (CIN)
unnamed: D242.6 (DOUT), D243.1 (DIN)
unnamed: D243.5 (COUT), D244.2 (CIN)
unnamed: D243.6 (DOUT), D244.1 (DIN)
unnamed: D244.5 (COUT), D245.2 (CIN)
unnamed: D244.6 (DOUT), D245.1 (DIN)
unnamed: D245.5 (COUT), D246.2 (CIN)
unnamed: D245.6 (DOUT), D246.1 (DIN)
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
